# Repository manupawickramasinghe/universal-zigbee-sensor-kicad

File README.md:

# Universal Zigbee Sensor Board (ESP32-H2-Supermini)

## Introduction

This repository contains the KiCad 9.0 project files for a universal Zigbee sensor board based on the ESP32-H2-Supermini module. This board is designed to be flexible and adaptable for various sensor applications, providing a compact and low-power solution for Zigbee-based IoT projects.

## Features

* **ESP32-H2-Supermini:** Utilizes the Espressif ESP32-H2-Supermini module, offering robust Zigbee connectivity and low power consumption.
* **Universal Sensor Interface:** Designed with multiple GPIO pins exposed for easy connection of various sensors (e.g., temperature, humidity, light, motion).
* **Power Supply Flexibility:** Supports various power supply options (e.g., battery, external power).
* **Compact Design:** Designed to be small and easily integrated into different enclosures.
* **KiCad 9.0 Project:** Fully documented project in KiCad 9.0 for easy modification and customization.

## Getting Started

### Prerequisites

* KiCad 9.0 or later installed.
* ESP32-H2-Supermini datasheet and documentation.
* Required sensor datasheets.
* A computer running a compatible operating system (Windows, macOS, Linux).

### Setup

1.  **Clone the Repository:**
    ```bash
    git clone https://github.com/manupawickramasinghe/universal-zigbee-sensor-kicad.git
    cd universal-zigbee-sensor-kicad
    ```
2.  **Open the Project in KiCad:**
    * Launch KiCad 9.0.
    * Click "File" -> "Open Project...".
    * Navigate to the cloned repository folder and select the `.kicad_pro` file.
3.  **Explore the Project:**
    * **Schematic Editor:** Open the schematic editor to view the circuit diagram. Examine the ESP32-H2-Supermini connections, sensor interfaces, and power supply circuitry.
    * **PCB Layout Editor:** Open the PCB layout editor to view the board layout. Inspect the component placement, routing, and board dimensions.
    * **Symbol and Footprint Libraries:** Ensure that the necessary symbol and footprint libraries are installed. The project should contain the needed libraries. However if you are missing any, they will need to be added.
4.  **Review the Datasheets:**
    * Refer to the ESP32-H2-Supermini datasheet to understand the pin functions and specifications.
    * Review the datasheets for the sensors you plan to use to ensure compatibility and proper connection.
5.  **Customize the Design (Optional):**
    * Modify the schematic and PCB layout to suit your specific sensor application.
    * Add or remove components as needed.
    * Adjust the routing and component placement for optimal performance.
6.  **Generate Gerber Files:**
    * Once you are satisfied with the design, generate Gerber files for PCB manufacturing.
    * In the PCB layout editor, click "File" -> "Fabrication Outputs" -> "Gerber Files...".
    * Configure the Gerber settings and generate the files.
7.  **Order PCBs:**
    * Use the generated Gerber files to order PCBs from a PCB manufacturer.
8.  **Assemble the Board:**
    * Solder the components onto the PCB.
    * Ensure proper orientation and soldering quality.
9.  **Programming the ESP32-H2-Supermini:**
    * Refer to the Espressif documentation for programming the ESP32-H2.
    * You will need a compatible development environment (e.g., ESP-IDF).
    * Develop and upload your firmware to the ESP32-H2-Supermini to control the sensors and manage Zigbee communication.
10. **Testing:**
    * Connect your sensors to the board.
    * Power up the board and test the functionality of the sensors and Zigbee communication.

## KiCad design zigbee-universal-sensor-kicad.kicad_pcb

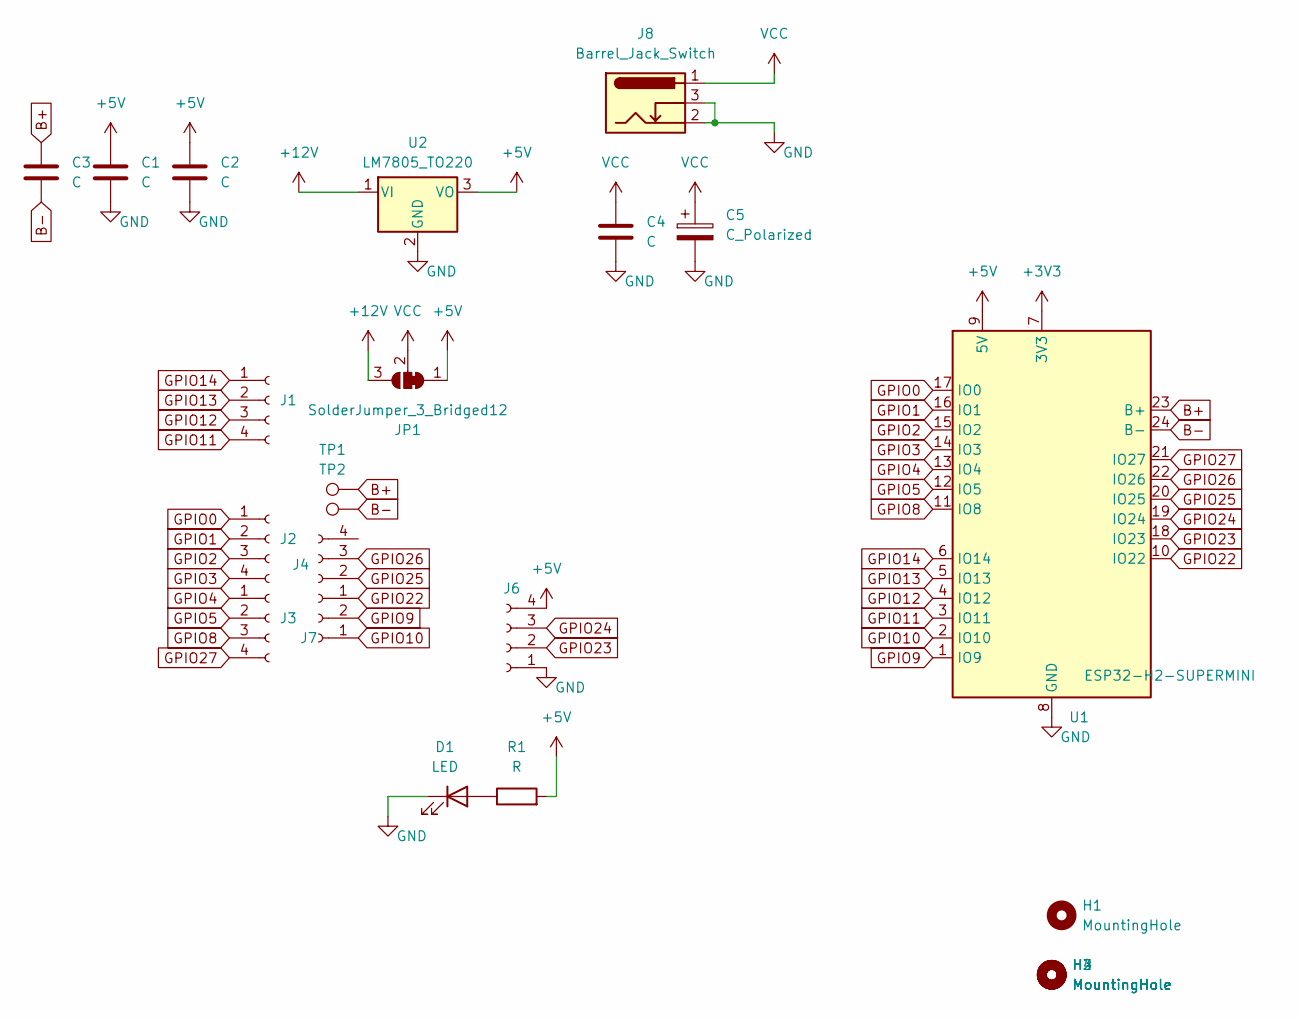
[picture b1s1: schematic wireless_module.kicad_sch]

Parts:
C1, C2, C3, C4: C; C_0805_2012Metric_Pad1.18x1.45mm_HandSolder
C5: C_Polarized; CP_Radial_D10.0mm_P3.80mm
D1: LED; LED_D4.0mm
H1, H2, H3, H4: MountingHole; MountingHole_2mm
J1, J2, J3, J4, J6: Conn_01x04_Socket; PinSocket_1x04_P2.54mm_Vertical
J7: Conn_01x02_Socket; PinSocket_1x02_P2.54mm_Vertical
J8: Barrel_Jack_Switch; BarrelJack_Horizontal
JP1: SolderJumper_3_Bridged12; SolderJumper-3_P1.3mm_Bridged12_Pad1.0x1.5mm
R1: R; R_0805_2012Metric_Pad1.20x1.40mm_HandSolder
TP1, TP2: TestPoint; TestPoint_Pad_D4.0mm
U1: ESP32-H2-SUPERMINI; ESP32H2-Supermini
U2: LM7805_TO220; TO-220-3_Vertical

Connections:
+3V3: U1.7 (3V3)
+5V: C1.1, C2.1, J6.4, JP1.1 (A), R1.2, U1.9 (5V), U2.3 (VO)
+12V: JP1.3 (B), U2.1 (VI)
B+: C3.1, TP1.1, U1.23 (B+)
B-: C3.2, TP2.1, U1.24 (B-)
GND: C1.2, C2.2, C4.2, C5.2, D1.1 (K), J6.1, J8.2, J8.3, U1.8 (GND), U2.2 (GND)
GPIO0: J2.1, U1.17 (IO0)
GPIO1: J2.2, U1.16 (IO1)
GPIO2: J2.3, U1.15 (IO2)
GPIO3: J2.4, U1.14 (IO3)
GPIO4: J3.1, U1.13 (IO4)
GPIO5: J3.2, U1.12 (IO5)
GPIO8: J3.3, U1.11 (IO8)
GPIO9: J7.2, U1.1 (IO9)
GPIO10: J7.1, U1.2 (IO10)
GPIO11: J1.4, U1.3 (IO11)
GPIO12: J1.3, U1.4 (IO12)
GPIO13: J1.2, U1.5 (IO13)
GPIO14: J1.1, U1.6 (IO14)
GPIO22: J4.1, U1.10 (IO22)
GPIO23: J6.2, U1.18 (IO23)
GPIO24: J6.3, U1.19 (IO24)
GPIO25: J4.2, U1.20 (IO25)
GPIO26: J4.3, U1.22 (IO26)
GPIO27: J3.4, U1.21 (IO27)
unnamed: D1.2 (A), R1.1
VCC: C4.1, C5.1, J8.1, JP1.2 (C)

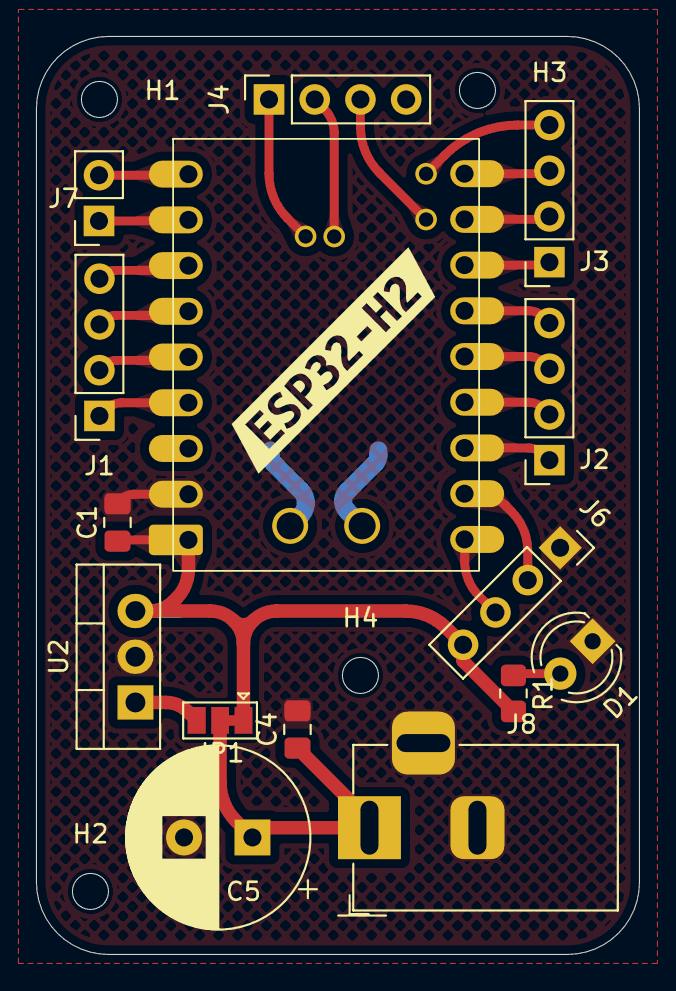
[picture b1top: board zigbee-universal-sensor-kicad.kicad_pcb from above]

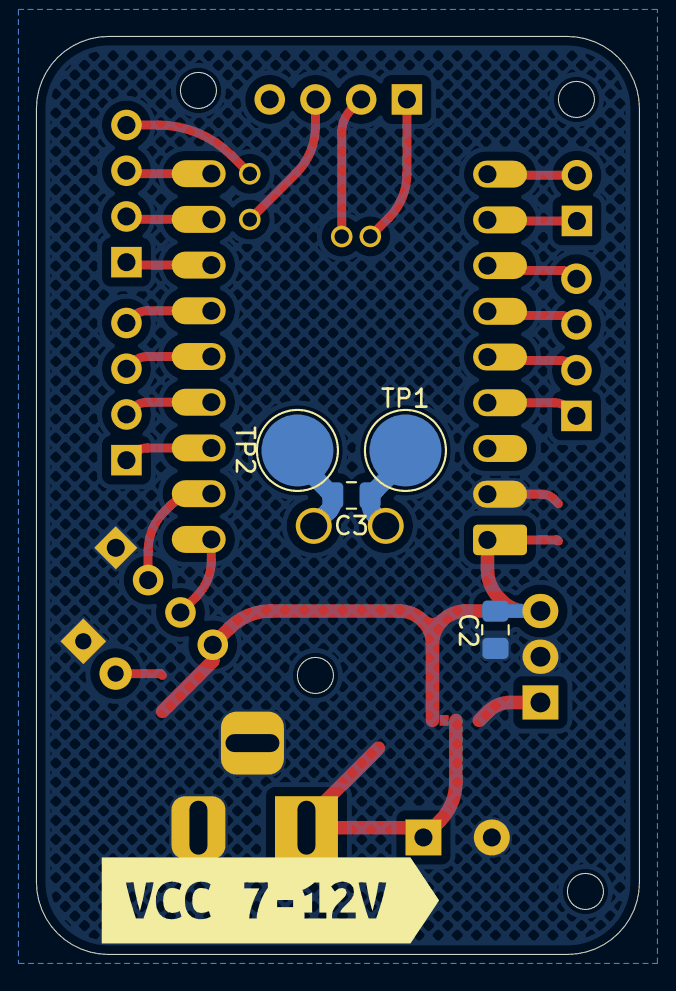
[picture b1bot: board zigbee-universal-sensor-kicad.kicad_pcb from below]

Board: 2 copper layers, 33.5 x 51.0 mm, 25 parts (5 on the bottom side), 26 nets.

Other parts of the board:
kibuzzard-67CC80C3: G***; kibuzzard-67CC80C3
kibuzzard-67CC814E: G***; kibuzzard-67CC814E
